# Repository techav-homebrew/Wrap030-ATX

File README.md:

# Wrap030
Homebrew mATX form-factor 68030 computer

# Memory Map

## Normal Operation
This is the space allocated to each device (even if the device will not use the entire address space allocated, such as the PS/2 keyboard controller which uses no address lines). 

| Device            | Start         | End           | Size                      |
| ----------------- | ------------- | ------------- | ------------------------- |
| Main Memory       | `$0000,0000`  | `$7fff,ffff`  | 2048MB (256MB available)  |
| Unused (BERR)     | `$8000,0000`  | `$cfff,ffff`  | 1280MB    |
| Video             | `$d000,0000`  | `$d0ff,ffff`  |   16MB    |
| Unused (BERR)     | `$d100,0000`  | `$d1ff,ffff`  |   16MB    |
| ISA Memory        | `$d200,0000`  | `$d2ff,ffff`  |   16MB    |
| ISA I/O           | `$d300,0000`  | `$d3ff,ffff`  |   16MB    |
| Unused (BERR)     | `$d400,0000`  | `$dbff,ffff`  |  128MB    |
| S/P I/O           | `$dc00,0000`  | `$dcff,ffff`  |   16MB    |
| Reserved (BERR)   | `$dd00,0000`  | `$ddff,ffff`  |   16MB    |
| Keyboard          | `$de00,0000`  | `$deff,ffff`  |   16MB    |
| Reserved (BERR)   | `$df00,0000`  | `$dfff,ffff`  |   16MB    |
| Bus Ctrl Reg      | `$e000,0000`  | `$e0ff,ffff`  |   16MB    |
| DRAM Ctrl Reg     | `$e100,0000`  | `$e1ff,ffff`  |   16MB    |
| IRQ Ctrl Reg      | `$e200,0000`  | `$e2ff,ffff`  |   16MB    |
| Unused (BERR)     | `$e300,0000`  | `$efff,ffff`  |  208MB    |
| ROM               | `$f000,0000`  | `$ffff,ffff`  |  256MB    |

## Reset Overlay
The reset overlay allows ROM to be read from the first 256MB of the CPU address space so the CPU can load the proper startup vectors. While the reset overlay is enabled, DRAM is write-only through the first 256MB (the entire DRAM space available on the Wrap030-ATX board). ROM will continue to be readable in its normal address space. This allows the reset vector to point to ROM at its normal address.

The reset overlay is enabled by default on power on. It is disabled by setting the overlay bit on the bus controller register. 

| Device            | Start         | End           | Notes                       |
| ----------------- | ------------- | ------------- | --------------------------- |
| ROM Overlay       | `$0000,0000`  | `$0fff,ffff`  | Read-only 256MB ROM space   |
| DRAM Overlay      | `$0000,0000`  | `$0fff,ffff`  | Write-Only 256MB DRAM space |
| DRAM              | `$1000,0000`  | `$7fff,ffff`  | Read/Write DRAM space       |
| ROM               | `$f000,0000`  | `$ffff,ffff`  | Read/Write ROM space        |

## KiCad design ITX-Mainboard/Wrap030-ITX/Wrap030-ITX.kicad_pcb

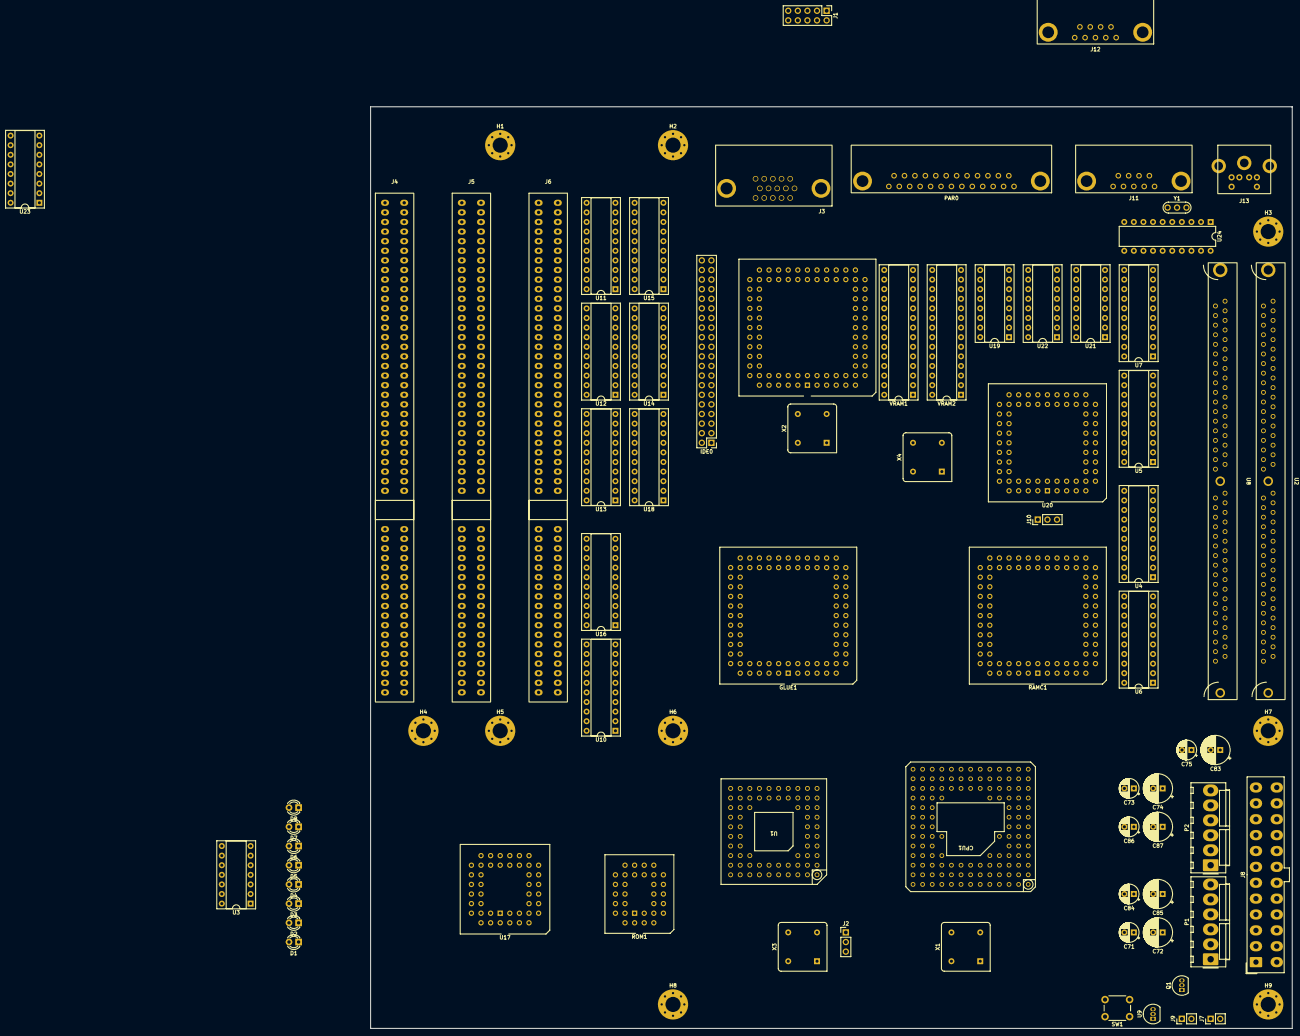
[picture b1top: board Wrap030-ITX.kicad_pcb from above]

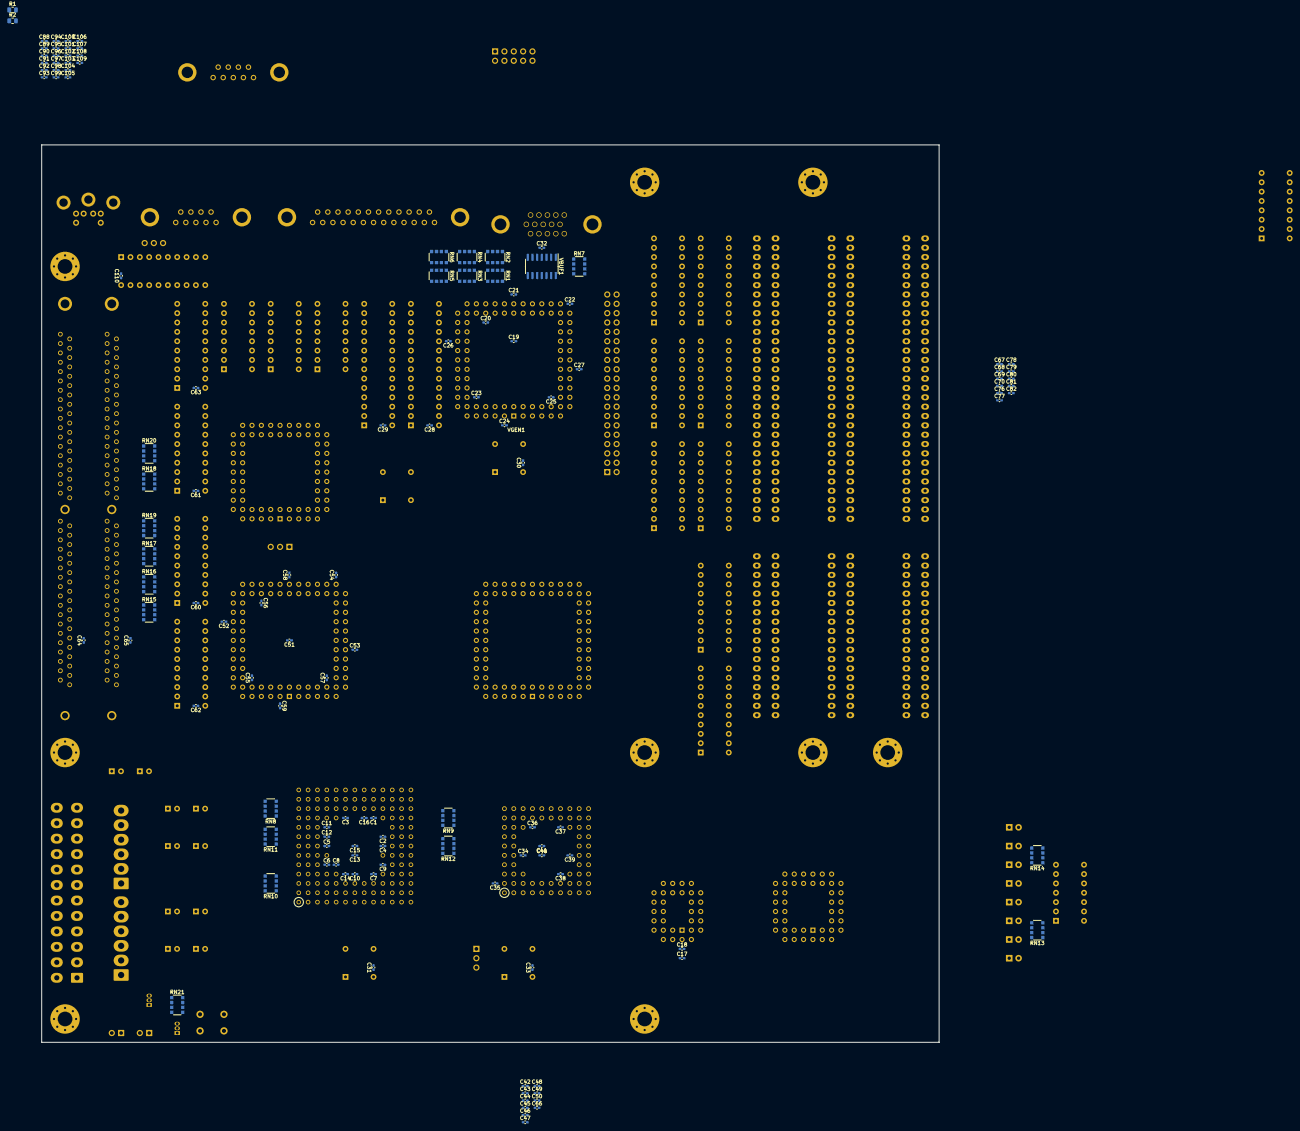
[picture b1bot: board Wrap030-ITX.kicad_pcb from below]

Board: 2 copper layers, 243.8 x 243.8 mm, 206 parts (124 on the bottom side), 386 nets, no tracks yet.

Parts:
C1, C2, C3, C4, C5, C6, C7, C8, C9, C10, C11, C12, C14, C16, C17, C20, C21, C22, C23, C24, C25, C26, C27, C28, C29, C30, C31, C32, C33, C34, C35, C36, C37, C38, C39, C43, C44, C45, C46, C47, C48, C49, C50, C52, C53, C54, C55, C56, C57, C58, C59, C60, C61, C62, C63, C66, C68, C69, C70, C76, C77, C78, C79, C80, C81, C82, C88, C89, C90, C91, C101, C110: 100nF; C_0402_1005Metric_Pad0.74x0.62mm_HandSolder
C13, C15, C18, C19, C40, C41, C42, C51, C64, C65, C67, C92, C102, C103, C104, C105, C106, C107, C108, C109: 1uF; C_0402_1005Metric_Pad0.74x0.62mm_HandSolder
C71, C73, C75, C84, C86: 10uF; CP_Radial_D5.0mm_P2.50mm
C72, C74, C83, C85, C87: 100uF; CP_Radial_D7.5mm_P2.50mm
C93, C94, C95, C96, C97, C98, C99, C100: 2200pF; C_0402_1005Metric_Pad0.74x0.62mm_HandSolder
CPU1: MC68030; PGA128
D1, D2, D3, D4, D5, D6, D7, D8: LED; LED_D3.0mm
GLUE1: ATF1508AS; PLCC-84_THT-Socket
H1, H2, H3, H4, H5, H6, H7, H8, H9: 4mm; MountingHole_4mm_Pad_Via
IDE0: Conn_02x20_Odd_Even; PinHeader_2x20_P2.54mm_Vertical
J1: Conn_02x05_Odd_Even; PinHeader_2x05_P2.54mm_Vertical
J2, J10: Conn_01x03; PinHeader_1x03_P2.54mm_Vertical
J3: DE15_Receptacle_HighDensity_MountingHoles; DE15-HD
J4, J5, J6: Bus_ISA_16bit; ISA16
J7, J9: Conn_01x02; PinHeader_1x02_P2.54mm_Vertical
J8: ATX-24; Molex_Mini-Fit_Jr_5566-24A_2x12_P4.20mm_Vertical
J11, J12: DE9_Plug_MountingHoles; DE9
J13: DIN-6; MiniDIN6
P1, P2: Conn_01x06; Molex_KK-396_A-41791-0006_1x06_P3.96mm_Vertical
PAR0: DB25_Receptacle_MountingHoles; DB25
Q1: PN2222A; TO-92L_Inline
R1, R2: 10k; R_0805_2012Metric
RAMC1: ATF1508AS; PLCC-84_THT-Socket
RN1, RN2, RN3, RN4, RN5, RN6, RN8, RN9, RN10, RN11, RN12: YC164-FR-071KL; R_Array_Convex_4x1206
RN7: YC164-FR-0775RL; R_Array_Convex_4x1206
RN13, RN14, RN21: YC124-JR-07220RL; R_Array_Convex_4x1206
RN15, RN16, RN17, RN18, RN19, RN20: YC124-JR-1033RL; R_Array_Convex_4x1206
ROM1: SST39SF040; PLCC-32_THT-Socket
SW1: SW_Push; SW_PUSH_6mm
U1: MC68882; PGA68
U2, U8: TE-822021-4; SIMM72
U3: 74HCT04; DIP-14_W7.62mm_Socket
U4, U5, U6, U7, U10, U11, U12: 74HC245; DIP-20_W7.62mm_Socket
U9: DS1813-5+T&R; TO-92_Inline
U13, U14, U15: 74LS573; DIP-20_W7.62mm_Socket
U16: 74AHCT244; DIP-20_W7.62mm_Socket
U17: ATF1504; PLCC-44_THT-Socket
U18: 74HCT688; DIP-20_W7.62mm_Socket
U19: 74LS139; DIP-16_W7.62mm_Socket
U20: WD16C552; PLCC-68_THT-Socket
U21, U22: MAX232; DIP-16_W7.62mm_Socket
U23: 74LS148; DIP-16_W7.62mm_Socket
U24: ATtiny2313A-PU; DIP-20_W7.62mm
VBUF1: ADA4891-4; SOIC-14_3.9x8.7mm_P1.27mm
VGEN1: ATF1508AS; PLCC-84_THT-Socket
VRAM1, VRAM2: CY62256-70PC; DIP-28_W7.62mm_Socket
X1: 50M; Oscillator_DIP-8
X2: 25.175M; Oscillator_DIP-8
X3: 16M; Oscillator_DIP-8
X4: 1.6862M; Oscillator_DIP-8
Y1: 16M; Resonator-3Pin_W7.0mm_H2.5mm

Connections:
+5VP: C75.1, C83.1, J8.9 (+5VSB), RN14.4 (R4.1)
+12V: C71.1, C72.1, J4.9 (+12V), J5.9 (+12V), J6.9 (+12V), J8.10 (+12V), J8.11 (+12V), P1.3
-5V: C86.2, C87.2, J4.5 (-5V), J5.5 (-5V), J6.5 (-5V), P2.3
-12V: C84.2, C85.2, J4.7 (-12V), J5.7 (-12V), J6.7 (-12V), J8.14 (-12V), P1.4
/CPU-FPU/FPU-CLK: J2.3, X3.5 (OUT)
/ISA-IDE/ISA-A0: IDE0.35, J4.62 (BA00), J5.62 (BA00), J6.62 (BA00), U13.19 (Q0)
/ISA-IDE/ISA-A1: IDE0.33, J4.61 (BA01), J5.61 (BA01), J6.61 (BA01), U13.18 (Q1)
/ISA-IDE/ISA-A2: IDE0.36, J4.60 (BA02), J5.60 (BA02), J6.60 (BA02), U13.17 (Q2)
/ISA-IDE/ISA-A3: J4.59 (BA03), J5.59 (BA03), J6.59 (BA03), U13.16 (Q3), U18.2 (P0)
/ISA-IDE/ISA-A4: J4.58 (BA04), J5.58 (BA04), J6.58 (BA04), U13.15 (Q4), U18.4 (P1)
/ISA-IDE/ISA-A5: J4.57 (BA05), J5.57 (BA05), J6.57 (BA05), U13.14 (Q5), U18.6 (P2)
/ISA-IDE/ISA-A6: J4.56 (BA06), J5.56 (BA06), J6.56 (BA06), U13.13 (Q6), U18.8 (P3)
/ISA-IDE/ISA-A7: J4.55 (BA07), J5.55 (BA07), J6.55 (BA07), U13.12 (Q7), U18.11 (P4)
/ISA-IDE/ISA-A8: J4.54 (BA08), J5.54 (BA08), J6.54 (BA08), U14.19 (Q0), U18.13 (P5)
/ISA-IDE/ISA-A9: J4.53 (BA09), J5.53 (BA09), J6.53 (BA09), U14.18 (Q1), U19.2 (A0)
/ISA-IDE/ISA-A10: J4.52 (BA10), J5.52 (BA10), J6.52 (BA10), U14.17 (Q2)
/ISA-IDE/ISA-A11: J4.51 (BA11), J5.51 (BA11), J6.51 (BA11), U14.16 (Q3)
/ISA-IDE/ISA-A12: J4.50 (BA12), J5.50 (BA12), J6.50 (BA12), U14.15 (Q4)
/ISA-IDE/ISA-A13: J4.49 (BA13), J5.49 (BA13), J6.49 (BA13), U14.14 (Q5)
/ISA-IDE/ISA-A14: J4.48 (BA14), J5.48 (BA14), J6.48 (BA14), U14.13 (Q6)
/ISA-IDE/ISA-A15: J4.47 (BA15), J5.47 (BA15), J6.47 (BA15), U14.12 (Q7)
/ISA-IDE/ISA-A16: J4.46 (BA16), J5.46 (BA16), J6.46 (BA16), U15.19 (Q0)
/ISA-IDE/ISA-A17: J4.45 (BA17), J5.45 (BA17), J6.45 (BA17), U15.18 (Q1)
/ISA-IDE/ISA-A18: J4.44 (BA18), J5.44 (BA18), J6.44 (BA18), U15.17 (Q2)
/ISA-IDE/ISA-A19: J4.43 (BA19), J5.43 (BA19), J6.43 (BA19), U15.16 (Q3)
/ISA-IDE/ISA-AEN: J4.28 (ALE), J5.28 (ALE), J6.28 (ALE), U13.1 (OE), U14.1 (OE), U15.1 (OE), U16.1 (1OE), U16.19 (2OE), U17.20 (IO19)
/ISA-IDE/ISA-ALE: J4.42 (AEN), J5.42 (AEN), J6.42 (AEN), U13.11 (Load), U14.11 (Load), U15.11 (Load), U17.21 (IO17)
/ISA-IDE/ISA-CLK: J4.20 (CLK), J5.20 (CLK), J6.20 (CLK), U17.25 (IO35)
/ISA-IDE/ISA-D0: IDE0.3, J4.40 (DB0), J5.40 (DB0), J6.40 (DB0), U11.2 (A0), U12.2 (A0)
/ISA-IDE/ISA-D1: IDE0.5, J4.39 (DB1), J5.39 (DB1), J6.39 (DB1), U11.3 (A1), U12.3 (A1)
/ISA-IDE/ISA-D2: IDE0.7, J4.38 (DB2), J5.38 (DB2), J6.38 (DB2), U11.4 (A2), U12.4 (A2)
/ISA-IDE/ISA-D3: IDE0.9, J4.37 (DB3), J5.37 (DB3), J6.37 (DB3), U11.5 (A3), U12.5 (A3)
/ISA-IDE/ISA-D4: IDE0.11, J4.36 (DB4), J5.36 (DB4), J6.36 (DB4), U11.6 (A4), U12.6 (A4)
/ISA-IDE/ISA-D5: IDE0.13, J4.35 (DB5), J5.35 (DB5), J6.35 (DB5), U11.7 (A5), U12.7 (A5)
/ISA-IDE/ISA-D6: IDE0.15, J4.34 (DB6), J5.34 (DB6), J6.34 (DB6), U11.8 (A6), U12.8 (A6)
/ISA-IDE/ISA-D7: IDE0.17, J4.33 (DB7), J5.33 (DB7), J6.33 (DB7), U11.9 (A7), U12.9 (A7)
/ISA-IDE/ISA-D8: IDE0.4, J4.91 (D8), J5.91 (D8), J6.91 (D8), U10.2 (A0)
/ISA-IDE/ISA-D9: IDE0.6, J4.92 (D9), J5.92 (D9), J6.92 (D9), U10.3 (A1)
/ISA-IDE/ISA-D10: IDE0.8, J4.93 (D10), J5.93 (D10), J6.93 (D10), U10.4 (A2)
/ISA-IDE/ISA-D11: IDE0.10, J4.94 (D11), J5.94 (D11), J6.94 (D11), U10.5 (A3)
/ISA-IDE/ISA-D12: IDE0.12, J4.95 (D12), J5.95 (D12), J6.95 (D12), U10.6 (A4)
/ISA-IDE/ISA-D13: IDE0.14, J4.96 (D13), J5.96 (D13), J6.96 (D13), U10.7 (A5)
/ISA-IDE/ISA-D14: IDE0.16, J4.97 (D14), J5.97 (D14), J6.97 (D14), U10.8 (A6)
/ISA-IDE/ISA-D15: IDE0.18, J4.98 (D15), J5.98 (D15), J6.98 (D15), U10.9 (A7)
/ISA-IDE/ISA-IDE-Connectors/ISA-OSC: J4.30 (OSC), J5.30 (OSC), J6.30 (OSC)
/ISA-IDE/ISA-IDE-Connectors/~IDE-DMACK: IDE0.29, R2.2
/ISA-IDE/ISA-IORDY: IDE0.27, J4.41 (IO_READY), J5.41 (IO_READY), J6.41 (IO_READY), R1.2, U17.29 (IO41)
/ISA-IDE/ISA-LA17: J4.88 (LA17), J5.88 (LA17), J6.88 (LA17), U16.18 (1Y0)
/ISA-IDE/ISA-LA18: J4.87 (LA18), J5.87 (LA18), J6.87 (LA18), U16.16 (1Y1)
/ISA-IDE/ISA-LA19: J4.86 (LA19), J5.86 (LA19), J6.86 (LA19), U16.14 (1Y2)
/ISA-IDE/ISA-LA20: J4.85 (LA20), J5.85 (LA20), J6.85 (LA20), U16.12 (1Y3)
/ISA-IDE/ISA-LA21: J4.84 (LA21), J5.84 (LA21), J6.84 (LA21), U16.3 (2Y0)
/ISA-IDE/ISA-LA22: J4.83 (LA22), J5.83 (LA22), J6.83 (LA22), U16.5 (2Y1)
/ISA-IDE/ISA-LA23: J4.82 (LA23), J5.82 (LA23), J6.82 (LA23), U16.7 (2Y2)
/ISA-IDE/ISA-MASTER: J4.79 (MASTER), J5.79 (MASTER), J6.79 (MASTER), U17.28 (IO40)
/ISA-IDE/ISA-RESET: IDE0.1, J4.2 (RESET), J5.2 (RESET), J6.2 (RESET), U17.19 (IO20)
/ISA-IDE/ISA-SBHE: J4.81 (SBHE), J5.81 (SBHE), J6.81 (SBHE), U17.18 (IO21)
/ISA-IDE/~IDE-CS1: IDE0.37, U19.4 (O0)
/ISA-IDE/~IDE-CS3: IDE0.38, U19.5 (O1)
/ISA-IDE/~ISA-IOCS16: IDE0.32, J4.64 (~IOCS16), J5.64 (~IOCS16), J6.64 (~IOCS16), U17.27 (IO37)
/ISA-IDE/~ISA-IOR: IDE0.25, J4.14 (~IOR), J5.14 (~IOR), J6.14 (~IOR), U17.24 (IO33)
/ISA-IDE/~ISA-IOW: IDE0.23, J4.13 (~IOW), J5.13 (~IOW), J6.13 (~IOW), U17.14 (IO30)
/ISA-IDE/~ISA-MEMCS16: J4.63 (~MEMCS16), J5.63 (~MEMCS16), J6.63 (~MEMCS16), U17.26 (IO36)
/ISA-IDE/~ISA-MEMR: J4.12 (~SMEMR), J4.89 (~MEMR), J5.12 (~SMEMR), J5.89 (~MEMR), J6.12 (~SMEMR), J6.89 (~MEMR), U17.17 (IO24)
/ISA-IDE/~ISA-MEMW: J4.11 (~SMEMW), J4.90 (~MEMW), J5.11 (~SMEMW), J5.90 (~MEMW), J6.11 (~SMEMW), J6.90 (~MEMW), U17.16 (IO25)
/ISA-IDE/~ISA-XFER8: U10.19 (CE), U17.5 (IO14)
/ISA-IDE/~ISA-XFER16: U11.19 (CE), U12.19 (CE), U17.4 (IO16)
/Keyboard/PS2-CLK: J13.5, U24.7 (PD3)
/Keyboard/PS2-DAT: J13.1, U24.8 (PD4)
/Main-Memory/MEM-A0: RAMC1.4 (IO16), RN15.1 (R1.1)
/Main-Memory/MEM-A0R: RN15.8 (R1.2), U2.12 (A0), U8.12 (A0)
/Main-Memory/MEM-A1: RAMC1.22 (IO17), RN15.2 (R2.1)
/Main-Memory/MEM-A1R: RN15.7 (R2.2), U2.13 (A1), U8.13 (A1)
/Main-Memory/MEM-A2: RAMC1.21 (IO19), RN15.3 (R3.1)
/Main-Memory/MEM-A2R: RN15.6 (R3.2), U2.14 (A2), U8.14 (A2)
/Main-Memory/MEM-A3: RAMC1.20 (IO21), RN15.4 (R4.1)
/Main-Memory/MEM-A3R: RN15.5 (R4.2), U2.15 (A3), U8.15 (A3)
/Main-Memory/MEM-A4: RAMC1.18 (IO24), RN16.1 (R1.1)
/Main-Memory/MEM-A4R: RN16.8 (R1.2), U2.16 (A4), U8.16 (A4)
/Main-Memory/MEM-A5: RAMC1.17 (IO25), RN16.2 (R2.1)
/Main-Memory/MEM-A5R: RN16.7 (R2.2), U2.17 (A5), U8.17 (A5)
/Main-Memory/MEM-A6: RAMC1.16 (IO27), RN16.3 (R3.1)
/Main-Memory/MEM-A6R: RN16.6 (R3.2), U2.18 (A6), U8.18 (A6)
/Main-Memory/MEM-A7: RAMC1.15 (IO29), RN16.4 (R4.1)
/Main-Memory/MEM-A7R: RN16.5 (R4.2), U2.28 (A7), U8.28 (A7)
/Main-Memory/MEM-A8: RAMC1.31 (IO35), RN17.1 (R1.1)
/Main-Memory/MEM-A8R: RN17.8 (R1.2), U2.31 (A8), U8.31 (A8)
/Main-Memory/MEM-A9: RAMC1.30 (IO37), RN17.2 (R2.1)
/Main-Memory/MEM-A9R: RN17.7 (R2.2), U2.32 (A9), U8.32 (A9)
/Main-Memory/MEM-A10: RAMC1.29 (IO38), RN17.3 (R3.1)
/Main-Memory/MEM-A10R: RN17.6 (R3.2), U2.19 (A10), U8.19 (A10)
/Main-Memory/MEM-A11: RAMC1.28 (IO40), RN17.4 (R4.1)
/Main-Memory/MEM-A11R: RN17.5 (R4.2), U2.29 (A11), U8.29 (A11)
/Main-Memory/MEM-D0: U2.2 (D0), U4.2 (A0), U8.2 (D0)
/Main-Memory/MEM-D1: U2.4 (D1), U4.3 (A1), U8.4 (D1)
/Main-Memory/MEM-D2: U2.6 (D2), U4.4 (A2), U8.6 (D2)
/Main-Memory/MEM-D3: U2.8 (D3), U4.5 (A3), U8.8 (D3)
/Main-Memory/MEM-D4: U2.20 (D4), U4.6 (A4), U8.20 (D4)
/Main-Memory/MEM-D5: U2.22 (D5), U4.7 (A5), U8.22 (D5)
/Main-Memory/MEM-D6: U2.24 (D6), U4.8 (A6), U8.24 (D6)
/Main-Memory/MEM-D7: U2.26 (D7), U4.9 (A7), U8.26 (D7)
/Main-Memory/MEM-D8: U2.49 (D8), U5.2 (A0), U8.49 (D8)
/Main-Memory/MEM-D9: U2.51 (D9), U5.3 (A1), U8.51 (D9)
/Main-Memory/MEM-D10: U2.53 (D10), U5.4 (A2), U8.53 (D10)
/Main-Memory/MEM-D11: U2.55 (D11), U5.5 (A3), U8.55 (D11)
/Main-Memory/MEM-D12: U2.57 (D12), U5.6 (A4), U8.57 (D12)
/Main-Memory/MEM-D13: U2.61 (D13), U5.7 (A5), U8.61 (D13)
/Main-Memory/MEM-D14: U2.63 (D14), U5.8 (A6), U8.63 (D14)
/Main-Memory/MEM-D15: U2.65 (D15), U5.9 (A7), U8.65 (D15)
/Main-Memory/MEM-D16: U2.3 (D16), U6.2 (A0), U8.3 (D16)
/Main-Memory/MEM-D17: U2.5 (D17), U6.3 (A1), U8.5 (D17)
/Main-Memory/MEM-D18: U2.7 (D18), U6.4 (A2), U8.7 (D18)
/Main-Memory/MEM-D19: U2.9 (D19), U6.5 (A3), U8.9 (D19)
/Main-Memory/MEM-D20: U2.21 (D20), U6.6 (A4), U8.21 (D20)
/Main-Memory/MEM-D21: U2.23 (D21), U6.7 (A5), U8.23 (D21)
/Main-Memory/MEM-D22: U2.25 (D22), U6.8 (A6), U8.25 (D22)
/Main-Memory/MEM-D23: U2.27 (D23), U6.9 (A7), U8.27 (D23)
/Main-Memory/MEM-D24: U2.50 (D24), U7.2 (A0), U8.50 (D24)
/Main-Memory/MEM-D25: U2.52 (D25), U7.3 (A1), U8.52 (D25)
/Main-Memory/MEM-D26: U2.54 (D26), U7.4 (A2), U8.54 (D26)
/Main-Memory/MEM-D27: U2.56 (D27), U7.5 (A3), U8.56 (D27)
/Main-Memory/MEM-D28: U2.58 (D28), U7.6 (A4), U8.58 (D28)
/Main-Memory/MEM-D29: U2.60 (D29), U7.7 (A5), U8.60 (D29)
/Main-Memory/MEM-D30: U2.62 (D30), U7.8 (A6), U8.62 (D30)
/Main-Memory/MEM-D31: U2.64 (D31), U7.9 (A7), U8.64 (D31)
/Main-Memory/~MEM-CAS0R: RN18.8 (R1.2), U2.40 (~CAS0), U8.40 (~CAS0)
/Main-Memory/~MEM-CAS0: RAMC1.40 (IO51), RN18.1 (R1.1)
/Main-Memory/~MEM-CAS1R: RN18.7 (R2.2), U2.43 (~CAS1), U8.43 (~CAS1)
/Main-Memory/~MEM-CAS1: RAMC1.39 (IO53), RN18.2 (R2.1)
/Main-Memory/~MEM-CAS2R: RN18.6 (R3.2), U2.41 (~CAS2), U8.41 (~CAS2)
/Main-Memory/~MEM-CAS2: RAMC1.37 (IO56), RN18.3 (R3.1)
/Main-Memory/~MEM-CAS3R: RN18.5 (R4.2), U2.42 (~CAS3), U8.42 (~CAS3)
/Main-Memory/~MEM-CAS3: RAMC1.36 (IO57), RN18.4 (R4.1)
/Main-Memory/~MEM-RAS0R: RN19.8 (R1.2), U2.34 (~RAS2), U2.44 (~RAS0)
/Main-Memory/~MEM-RAS0: RAMC1.27 (IO43), RN19.1 (R1.1)
/Main-Memory/~MEM-RAS1R: RN19.7 (R2.2), U2.33 (~RAS3), U2.45 (~RAS1)
/Main-Memory/~MEM-RAS1: RAMC1.25 (IO45), RN19.2 (R2.1)
/Main-Memory/~MEM-RAS2R: RN19.6 (R3.2), U8.34 (~RAS2), U8.44 (~RAS0)
/Main-Memory/~MEM-RAS2: RAMC1.24 (IO46), RN19.3 (R3.1)
/Main-Memory/~MEM-RAS3R: RN19.5 (R4.2), U8.33 (~RAS3), U8.45 (~RAS1)
/Main-Memory/~MEM-RAS3: RAMC1.41 (IO49), RN19.4 (R4.1)
/Main-Memory/~MEM-WER: RN20.8 (R1.2), U2.47 (~WE), U8.47 (~WE)
/Main-Memory/~MEM-WE: RAMC1.35 (IO59), RN20.1 (R1.1), U4.1 (A->B), U5.1 (A->B), U6.1 (A->B), U7.1 (A->B)
/Power-Supply/PWR_ON_R: Q1.2 (B), RN21.8 (R1.2)
/Power-Supply/~PWR_ON: J7.2, J8.16 (PS_ON#), Q1.3 (C)
/Serial-Parallel-IO/COM0-C1M: C102.2, U21.3 (C1-)
/Serial-Parallel-IO/COM0-C1P: C102.1, U21.1 (C1+)
/Serial-Parallel-IO/COM0-C2M: C103.1, U21.5 (C2-)
/Serial-Parallel-IO/COM0-C2P: C103.2, U21.4 (C2+)
/Serial-Parallel-IO/COM0-CTS232: J11.8, U21.8 (R2IN)
/Serial-Parallel-IO/COM0-RTS232: J11.7, U21.7 (T2OUT)
/Serial-Parallel-IO/COM0-RX232: J11.2, U21.13 (R1IN)
/Serial-Parallel-IO/COM0-SIN: U20.41 (SIN0), U21.12 (R1OUT)
/Serial-Parallel-IO/COM0-SOUT: U20.26 (SOUT0), U21.11 (T1IN)
/Serial-Parallel-IO/COM0-TX232: J11.3, U21.14 (T1OUT)
/Serial-Parallel-IO/COM0-VM: C105.1, U21.6 (VS-)
/Serial-Parallel-IO/COM0-VP: C104.1, U21.2 (VS+)
/Serial-Parallel-IO/COM1-C1M: C106.2, U22.3 (C1-)
/Serial-Parallel-IO/COM1-C1P: C106.1, U22.1 (C1+)
/Serial-Parallel-IO/COM1-C2M: C109.1, U22.5 (C2-)
/Serial-Parallel-IO/COM1-C2P: C109.2, U22.4 (C2+)
/Serial-Parallel-IO/COM1-CTS232: J12.8, U22.8 (R2IN)
/Serial-Parallel-IO/COM1-RTS232: J12.7, U22.7 (T2OUT)
/Serial-Parallel-IO/COM1-RX232: J12.2, U22.13 (R1IN)
/Serial-Parallel-IO/COM1-SIN: U20.62 (SIN1), U22.12 (R1OUT)
/Serial-Parallel-IO/COM1-SOUT: U20.10 (SOUT1), U22.11 (T1IN)
/Serial-Parallel-IO/COM1-TX232: J12.3, U22.14 (T1OUT)
/Serial-Parallel-IO/COM1-VM: C108.1, U22.6 (VS-)
/Serial-Parallel-IO/COM1-VP: C107.1, U22.2 (VS+)
/Serial-Parallel-IO/PAR-BIDEN: J10.2, U20.1 (BIDEN)
/Serial-Parallel-IO/PAR-BUSY: PAR0.11, U20.66 (BUSY)
/Serial-Parallel-IO/PAR-D0: C93.1, U20.53 (PD0)
/Serial-Parallel-IO/PAR-D0-C: C93.2, PAR0.2
/Serial-Parallel-IO/PAR-D1: C94.1, U20.52 (PD1)
/Serial-Parallel-IO/PAR-D1-C: C94.2, PAR0.3
/Serial-Parallel-IO/PAR-D2: C95.1, U20.51 (PD2)
/Serial-Parallel-IO/PAR-D2-C: C95.2, PAR0.4
/Serial-Parallel-IO/PAR-D3: C96.1, U20.50 (PD3)
/Serial-Parallel-IO/PAR-D3-C: C96.2, PAR0.5
/Serial-Parallel-IO/PAR-D4: C97.1, U20.49 (PD4)
/Serial-Parallel-IO/PAR-D4-C: C97.2, PAR0.6
/Serial-Parallel-IO/PAR-D5: C98.1, U20.48 (PD5)
/Serial-Parallel-IO/PAR-D5-C: C98.2, PAR0.7
/Serial-Parallel-IO/PAR-D6: C99.1, U20.47 (PD6)
/Serial-Parallel-IO/PAR-D6-C: C99.2, PAR0.8
/Serial-Parallel-IO/PAR-D7: C100.1, U20.46 (PD7)
/Serial-Parallel-IO/PAR-D7-C: C100.2, PAR0.9
/Serial-Parallel-IO/PAR-PE: PAR0.12, U20.67 (PE)
/Serial-Parallel-IO/PAR-SLCT: PAR0.13, U20.65 (SLCT)
/Serial-Parallel-IO/SPIO-CLK: U20.4 (COM-CLK), X4.5 (OUT)
/Serial-Parallel-IO/~COM0-CTS: U20.28 (~CTS0), U21.9 (R2OUT)
/Serial-Parallel-IO/~COM0-RTS: U20.24 (~RTS0), U21.10 (T2IN)
/Serial-Parallel-IO/~COM1-CTS: U20.13 (~CTS1), U22.9 (R2OUT)
/Serial-Parallel-IO/~COM1-RTS: U20.12 (~RTS1), U22.10 (T2IN)
/Serial-Parallel-IO/~PAR-ACK: PAR0.10, U20.68 (~ACK)
/Serial-Parallel-IO/~PAR-AFD: PAR0.14, U20.56 (~AFD)
/Serial-Parallel-IO/~PAR-ERR: PAR0.15, U20.63 (~ERR)
/Serial-Parallel-IO/~PAR-INIT: PAR0.16, U20.57 (~INIT)
/Serial-Parallel-IO/~PAR-SLIN: PAR0.17, U20.58 (~SLIN)
/Serial-Parallel-IO/~PAR-STB: PAR0.1, U20.55 (~STB)
/Serial-Parallel-IO/~SPIO-CS0: U19.12 (O0), U20.32 (~CS0)
/Serial-Parallel-IO/~SPIO-CS1: U19.11 (O1), U20.3 (~CS1)
/Serial-Parallel-IO/~SPIO-CS2: U19.10 (O2), U20.38 (~CS2)
/VidGen/VID-B-A: RN5.2 (R2.1), RN5.3 (R3.1), RN5.4 (R4.1), VBUF1.12 (IN4_P)
/VidGen/VID-B-D: RN5.1 (R1.1), VGEN1.51 (IO77)
/VidGen/VID-B-D1: RN5.7 (R2.2), RN5.8 (R1.2)
/VidGen/VID-B-OUT: J1.6, J3.3, RN7.6 (R3.2)
/VidGen/VID-G-A: RN3.2 (R2.1), RN3.3 (R3.1), RN3.4 (R4.1), VBUF1.10 (IN3_P)
/VidGen/VID-G-D: RN3.1 (R1.1), VGEN1.49 (IO73)
/VidGen/VID-G-D1: RN3.7 (R2.2), RN3.8 (R1.2)
/VidGen/VID-G-OUT: J1.8, J3.2, RN7.7 (R2.2)
/VidGen/VID-H: J1.4, J3.13, VGEN1.50 (IO75)
/VidGen/VID-I-D: RN2.7 (R2.2), RN4.7 (R2.2), RN6.7 (R2.2), VGEN1.46 (IO69)
/VidGen/VID-I-D1B: RN6.1 (R1.1), RN6.2 (R2.1)
/VidGen/VID-I-D1G: RN4.1 (R1.1), RN4.2 (R2.1)
/VidGen/VID-I-D1R: RN2.1 (R1.1), RN2.2 (R2.1)
/VidGen/VID-I-D2B: RN5.6 (R3.2), RN6.6 (R3.2), RN6.8 (R1.2)
/VidGen/VID-I-D2G: RN3.6 (R3.2), RN4.6 (R3.2), RN4.8 (R1.2)
/VidGen/VID-I-D2R: RN1.6 (R3.2), RN2.6 (R3.2), RN2.8 (R1.2)
/VidGen/VID-I-D3B: RN6.3 (R3.1), RN6.4 (R4.1)
/VidGen/VID-I-D3G: RN4.3 (R3.1), RN4.4 (R4.1)
/VidGen/VID-I-D3R: RN2.3 (R3.1), RN2.4 (R4.1)
/VidGen/VID-R-A: RN1.2 (R2.1), RN1.3 (R3.1), RN1.4 (R4.1), VBUF1.5 (IN2_P)
/VidGen/VID-R-D: RN1.1 (R1.1), VGEN1.45 (IO67)
/VidGen/VID-R-D1: RN1.7 (R2.2), RN1.8 (R1.2)
/VidGen/VID-R-OUT: J1.10, J3.1, RN7.8 (R1.2)
/VidGen/VID-V: J1.2, J3.14, VGEN1.48 (IO72)
/VidGen/VID_A0: VGEN1.30 (IO37), VRAM1.10 (A0), VRAM2.10 (A0)
/VidGen/VID_A1: VGEN1.28 (IO40), VRAM1.9 (A1), VRAM2.9 (A1)
/VidGen/VID_A2: VGEN1.27 (IO43), VRAM1.8 (A2), VRAM2.8 (A2)
/VidGen/VID_A3: VGEN1.25 (IO45), VRAM1.7 (A3), VRAM2.7 (A3)
/VidGen/VID_A4: VGEN1.21 (IO19), VRAM1.6 (A4), VRAM2.6 (A4)
/VidGen/VID_A5: VGEN1.8 (IO11), VRAM1.5 (A5), VRAM2.5 (A5)
/VidGen/VID_A6: VGEN1.17 (IO25), VRAM1.4 (A6), VRAM2.4 (A6)
/VidGen/VID_A7: VGEN1.10 (IO6), VRAM1.3 (A7), VRAM2.3 (A7)
/VidGen/VID_A8: VGEN1.16 (IO27), VRAM1.25 (A8), VRAM2.25 (A8)
/VidGen/VID_A9: VGEN1.18 (IO24), VRAM1.24 (A9), VRAM2.24 (A9)
/VidGen/VID_A10: VGEN1.24 (IO46), VRAM1.21 (A10), VRAM2.21 (A10)
/VidGen/VID_A11: VGEN1.20 (IO21), VRAM1.23 (A11), VRAM2.23 (A11)
/VidGen/VID_A12: VGEN1.11 (IO5), VRAM1.2 (A12), VRAM2.2 (A12)
/VidGen/VID_A13: VGEN1.15 (IO29), VRAM1.26 (A13), VRAM2.26 (A13)
/VidGen/VID_A14: VGEN1.9 (IO8), VRAM1.1 (A14), VRAM2.1 (A14)
/VidGen/VID_CLK: VGEN1.83 (GCLK1), X2.5 (OUT)
/VidGen/VID_D0: VGEN1.34 (IO61), VRAM1.11 (Q0), VRAM2.11 (Q0)
/VidGen/VID_D1: VGEN1.35 (IO59), VRAM1.12 (Q1), VRAM2.12 (Q1)
/VidGen/VID_D2: VGEN1.40 (IO51), VRAM1.13 (Q2), VRAM2.13 (Q2)
/VidGen/VID_D3: VGEN1.39 (IO53), VRAM1.15 (Q3), VRAM2.15 (Q3)
/VidGen/VID_D4: VGEN1.37 (IO56), VRAM1.16 (Q4), VRAM2.16 (Q4)
/VidGen/VID_D5: VGEN1.33 (IO64), VRAM1.17 (Q5), VRAM2.17 (Q5)
/VidGen/VID_D6: VGEN1.36 (IO57), VRAM1.18 (Q6), VRAM2.18 (Q6)
/VidGen/VID_D7: VGEN1.31 (IO35), VRAM1.19 (Q7), VRAM2.19 (Q7)
/VidGen/~VID_CS0: VGEN1.29 (IO38), VRAM1.20 (~CS)
/VidGen/~VID_CS1: VGEN1.44 (IO65), VRAM2.20 (~CS)
/VidGen/~VID_RD: VGEN1.22 (IO17), VRAM1.22 (~OE), VRAM2.22 (~OE)
/VidGen/~VID_WR: VGEN1.12 (IO3), VRAM1.27 (~WE), VRAM2.27 (~WE)
CPU-A0: CPU1.A2 (A0), GLUE1.65 (IO101), RAMC1.44 (IO65), ROM1.12 (A0), U13.2 (D0), VGEN1.4 (IO16)
CPU-A1: CPU1.C4 (A1), GLUE1.67 (IO104), RAMC1.45 (IO67), ROM1.11 (A1), U1.K1 (A1), U13.3 (D1), VGEN1.55 (IO85)
CPU-A2: CPU1.D13 (A2), RAMC1.46 (IO69), ROM1.10 (A2), U1.H2 (A2), U13.4 (D2), VGEN1.54 (IO83)
CPU-A3: CPU1.D12 (A3), RAMC1.48 (IO72), ROM1.9 (A3), U1.J1 (A3), U13.5 (D3), U20.35 (A0), VGEN1.57 (IO88)
CPU-A4: CPU1.C13 (A4), RAMC1.49 (IO73), ROM1.8 (A4), U1.G2 (A4), U13.6 (D4), U20.34 (A1), VGEN1.56 (IO86)
CPU-A5: CPU1.C12 (A5), RAMC1.50 (IO75), ROM1.7 (A5), U13.7 (D5), U20.33 (A2), VGEN1.58 (IO91)
CPU-A6: CPU1.D11 (A6), RAMC1.51 (IO77), ROM1.6 (A6), U13.8 (D6), U19.13 (A1), VGEN1.61 (IO94)
CPU-A7: CPU1.B13 (A7), RAMC1.52 (IO80), ROM1.5 (A7), U13.9 (D7), U19.14 (A0), VGEN1.60 (IO93)
CPU-A8: CPU1.B12 (A8), RAMC1.54 (IO83), ROM1.27 (A8), U14.2 (D0), VGEN1.63 (IO97)
CPU-A9: CPU1.C11 (A9), RAMC1.55 (IO85), ROM1.26 (A9), U14.3 (D1), VGEN1.65 (IO101)
CPU-A10: CPU1.A13 (A10), RAMC1.56 (IO86), ROM1.23 (A10), U14.4 (D2), VGEN1.64 (IO99)
CPU-A11: CPU1.C10 (A11), RAMC1.57 (IO88), ROM1.25 (A11), U14.5 (D3), VGEN1.67 (IO104)
CPU-A12: CPU1.B11 (A12), RAMC1.58 (IO91), ROM1.4 (A12), U14.6 (D4), VGEN1.68 (IO105)
CPU-A13: CPU1.A12 (A13), RAMC1.60 (IO93), ROM1.28 (A13), U14.7 (D5), VGEN1.69 (IO107)
CPU-A14: CPU1.B10 (A14), RAMC1.61 (IO94), ROM1.29 (A14), U14.8 (D6), VGEN1.70 (IO109)
CPU-A15: CPU1.A11 (A15), RAMC1.63 (IO97), ROM1.3 (A15), U14.9 (D7), VGEN1.52 (IO80)
CPU-A16: CPU1.B9 (A16), RAMC1.64 (IO99), ROM1.2 (A16), U15.2 (D0)
CPU-A17: CPU1.A10 (A17), RAMC1.65 (IO101), ROM1.30 (A17), U15.3 (D1), U16.2 (1A0)
CPU-A18: CPU1.C8 (A18), RAMC1.67 (IO104), ROM1.1 (A18), U15.4 (D2), U16.4 (1A1)
CPU-A19: CPU1.A9 (A19), RAMC1.68 (IO105), U15.5 (D3), U16.6 (1A2)
CPU-A20: CPU1.B8 (A20), RAMC1.69 (IO107), U16.8 (1A3)
CPU-A21: CPU1.A8 (A21), GLUE1.68 (IO105), RAMC1.70 (IO109), U16.17 (2A0)
CPU-A22: CPU1.B7 (A22), GLUE1.69 (IO107), RAMC1.73 (IO115), U16.15 (2A1)
CPU-A23: CPU1.A7 (A23), GLUE1.70 (IO109), RAMC1.74 (IO117), U16.13 (2A2)
CPU-A24: CPU1.A6 (A24), GLUE1.73 (IO115), RAMC1.75 (IO118)
CPU-A25: CPU1.B6 (A25), GLUE1.74 (IO117), RAMC1.76 (IO120)
CPU-A26: CPU1.A5 (A26), GLUE1.75 (IO118), RAMC1.77 (IO123)
CPU-A27: CPU1.B5 (A27), GLUE1.76 (IO120), RAMC1.79 (IO125)
CPU-A28: CPU1.A4 (A28), GLUE1.77 (IO123), RAMC1.80 (IO126)
CPU-A29: CPU1.B4 (A29), GLUE1.79 (IO125), RAMC1.81 (IO128)
CPU-A30: CPU1.A3 (A30), GLUE1.80 (IO126)
CPU-A31: CPU1.B3 (A31), GLUE1.81 (IO128)
CPU-CLK: CPU1.E1 (CLK), GLUE1.83 (GCLK1), J2.1, RAMC1.83 (GCLK1), U17.43 (GCLK1), X1.5 (OUT)
CPU-D0: CPU1.K13 (D0), U1.A3 (D0), U4.18 (B0)
CPU-D1: CPU1.K12 (D1), U1.A4 (D1), U4.17 (B1)
CPU-D2: CPU1.L13 (D2), U1.B5 (D2), U4.16 (B2)
CPU-D3: CPU1.M13 (D3), U1.A5 (D3), U4.15 (B3)
CPU-D4: CPU1.L12 (D4), U1.A6 (D4), U4.14 (B4)
CPU-D5: CPU1.K11 (D5), U1.B6 (D5), U4.13 (B5)
CPU-D6: CPU1.M12 (D6), U1.A7 (D6), U4.12 (B6)
CPU-D7: CPU1.L11 (D7), U1.A8 (D7), U4.11 (B7)
CPU-D8: CPU1.N13 (D8), U1.A9 (D8), U5.18 (B0)
CPU-D9: CPU1.M11 (D9), U1.C8 (D9), U5.17 (B1)
CPU-D10: CPU1.L10 (D10), U1.B9 (D10), U5.16 (B2)
CPU-D11: CPU1.N12 (D11), U1.B10 (D11), U5.15 (B3)
CPU-D12: CPU1.M10 (D12), U1.D9 (D12), U5.14 (B4)
CPU-D13: CPU1.N11 (D13), U1.C9 (D13), U5.13 (B5)
CPU-D14: CPU1.M9 (D14), U1.C10 (D14), U5.12 (B6)
CPU-D15: CPU1.N10 (D15), U1.D10 (D15), U5.11 (B7)
CPU-D16: CPU1.N9 (D16), U1.F10 (D16), U6.18 (B0), U11.18 (B0)
CPU-D17: CPU1.M8 (D17), U1.F9 (D17), U6.17 (B1), U11.17 (B1)
CPU-D18: CPU1.N8 (D18), U1.G10 (D18), U6.16 (B2), U11.16 (B2)
CPU-D19: CPU1.N7 (D19), U1.H10 (D19), U6.15 (B3), U11.15 (B3)
CPU-D20: CPU1.M7 (D20), U1.G9 (D20), U6.14 (B4), U11.14 (B4)
CPU-D21: CPU1.N6 (D21), U1.J10 (D21), U6.13 (B5), U11.13 (B5)
CPU-D22: CPU1.M6 (D22), U1.K10 (D22), U6.12 (B6), U11.12 (B6)
CPU-D23: CPU1.N5 (D23), U1.J9 (D23), U6.11 (B7), U11.11 (B7)
CPU-D24: CPU1.M5 (D24), GLUE1.44 (IO65), ROM1.13 (D0), U1.K9 (D24), U7.18 (B0), U10.18 (B0), U12.18 (B0), U20.14 (D0), U24.12 (PB0), VGEN1.73 (IO115)
CPU-D25: CPU1.N4 (D25), GLUE1.45 (IO67), ROM1.14 (D1), U1.J7 (D25), U7.17 (B1), U10.17 (B1), U12.17 (B1), U20.15 (D1), U24.13 (PB1), VGEN1.74 (IO117)
CPU-D26: CPU1.N3 (D26), GLUE1.46 (IO69), ROM1.15 (D2), U1.K8 (D26), U7.16 (B2), U10.16 (B2), U12.16 (B2), U20.16 (D2), U24.14 (PB2), VGEN1.76 (IO120)
CPU-D27: CPU1.M4 (D27), GLUE1.48 (IO72), ROM1.17 (D3), U1.K7 (D27), U7.15 (B3), U10.15 (B3), U12.15 (B3), U20.17 (D3), U24.15 (PB3), VGEN1.75 (IO118)
CPU-D28: CPU1.N2 (D28), GLUE1.49 (IO73), ROM1.18 (D4), U1.J6 (D28), U7.14 (B4), U10.14 (B4), U12.14 (B4), U20.18 (D4), U24.16 (PB4), VGEN1.77 (IO123)
CPU-D29: CPU1.M3 (D29), GLUE1.50 (IO75), ROM1.19 (D5), U1.K6 (D29), U7.13 (B5), U10.13 (B5), U12.13 (B5), U20.19 (D5), U24.17 (PB5), VGEN1.80 (IO126)
CPU-D30: CPU1.L4 (D30), GLUE1.51 (IO77), ROM1.20 (D6), U1.K5 (D30), U7.12 (B6), U10.12 (B6), U12.12 (B6), U20.20 (D6), U24.18 (PB6), VGEN1.79 (IO125)
CPU-D31: CPU1.N1 (D31), GLUE1.52 (IO80), ROM1.21 (D7), U1.J5 (D31), U7.11 (B7), U10.11 (B7), U12.11 (B7), U20.21 (D7), U24.19 (PB7), VGEN1.81 (IO128)
FC0: CPU1.D2 (FC0), GLUE1.12 (IO3), RAMC1.12 (IO3)
FC1: CPU1.C1 (FC1), GLUE1.11 (IO5), RAMC1.11 (IO5)
FC2: CPU1.D1 (FC2), GLUE1.10 (IO6), RAMC1.10 (IO6)
GND: C1.2, C2.2, C3.2, C4.2, C5.2, C6.2, C7.2, C8.2, C9.2, C10.2, C11.2, C12.2, C13.2, C14.2, C15.2, C16.2, C17.2, C18.2, C19.2, C20.2, C21.2, C22.2, C23.2, C24.2, C25.2, C26.2, C27.2, C28.2, C29.2, C30.2, C31.2, C32.2, C33.2, C34.2, C35.2, C36.2, C37.2, C38.2, C39.2, C40.2, C41.2, C42.2, C43.2, C44.2, C45.2, C46.2, C47.2, C48.2, C49.2, C50.2, C51.2, C52.2, C53.2, C54.2, C55.2, C56.2, C57.2, C58.2, C59.2, C60.2, C61.2, C62.2, C63.2, C64.2, C65.2, C66.2, C67.2, C68.2, C69.2, C70.2, C71.2, C72.2, C73.2, C74.2, C75.2, C76.2, C77.2, C78.2, C79.2, C80.2, C81.2, C82.2, C83.2, C84.1, C85.1, C86.1, C87.1, C88.2, C89.2, C90.2, C91.2, C92.2, C101.2, C105.2, C108.2, C110.2, CPU1.C5 (GND), CPU1.C7 (GND), CPU1.C9 (GND), CPU1.E3 (GND), CPU1.E11 (GND), CPU1.F3 (GND), CPU1.G3 (GND), CPU1.G11 (GND), CPU1.J3 (GND), CPU1.J11 (GND), CPU1.L5 (GND), CPU1.L7 (GND), CPU1.L8 (GND), CPU1.L9 (GND), D1.1 (K), D2.1 (K), D3.1 (K), D4.1 (K), D5.1 (K), D6.1 (K), D7.1 (K), D8.1 (K), GLUE1.7 (GND), GLUE1.19 (GND), GLUE1.32 (GND), GLUE1.42 (GND), GLUE1.47 (GND), GLUE1.59 (GND), GLUE1.72 (GND), GLUE1.82 (GND), H1.1, H2.1, H3.1, H4.1, H5.1, H6.1, H7.1, H8.1, H9.1, IDE0.2, IDE0.19, IDE0.22, IDE0.24, IDE0.26, IDE0.30, IDE0.40, J1.1, J1.3, J1.5, J1.7, J1.9, J3.5, J3.6, J3.7, J3.8, J3.10, J4.1 (GND), J4.31 (GND), J4.80 (GND), J5.1 (GND), J5.31 (GND), J5.80 (GND), J6.1 (GND), J6.31 (GND), J6.80 (GND), J7.1, J8.3 (GND), J8.5 (GND), J8.7 (GND), J8.15 (GND), J8.17 (GND), J8.18 (GND), J8.19 (GND), J8.24 (GND), J9.1, J10.3, J11.5, J12.5, J13.3, P1.5, P1.6, P2.1, P2.2, PAR0.18, PAR0.19, PAR0.20, PAR0.21, PAR0.22, PAR0.23, PAR0.24, PAR0.25, Q1.1 (E), RAMC1.7 (GND), RAMC1.19 (GND), RAMC1.32 (GND), RAMC1.42 (GND), RAMC1.47 (GND), RAMC1.59 (GND), RAMC1.72 (GND), RAMC1.82 (GND), RN1.5 (R4.2), RN2.5 (R4.2), RN3.5 (R4.2), RN4.5 (R4.2), RN5.5 (R4.2), RN6.5 (R4.2), ROM1.16 (GND), SW1.2, U1.A2 (GND), U1.A10 (GND), U1.B2 (GND), U1.B3 (GND), U1.B7 (GND), U1.C1 (GND), U1.C3 (GND), U1.D2 (GND), U1.E10 (GND), U1.F2 (GND), U1.H9 (GND), U1.J8 (GND), U1.K3 (GND), U2.1 (VSS), U2.39 (VSS), U2.72 (VSS), U3.7 (GND), U4.10 (GND), U5.10 (GND), U6.10 (GND), U7.10 (GND), U8.1 (VSS), U8.39 (VSS), U8.72 (VSS), U9.3 (GND), U10.10 (GND), U11.10 (GND), U12.10 (GND), U13.10 (GND), U14.10 (GND), U15.6 (D4), U15.7 (D5), U15.8 (D6), U15.9 (D7), U15.10 (GND), U16.10 (GND), U16.11 (2A3), U17.10 (GND), U17.22 (GND), U17.30 (GND), U17.42 (GND), U18.1 (G), U18.3 (R0), U18.10 (GND), U18.15 (P6), U18.16 (R6), U18.17 (P7), U18.18 (R7), U19.3 (A1), U19.8 (GND), U20.2 (GND), U20.7 (GND), U20.43 (GND), U20.54 (GND), U21.15 (GND), U22.15 (GND), U23.5 (EI), U23.8 (GND), U24.10 (GND), VBUF1.11 (GND), VGEN1.7 (GND), VGEN1.19 (GND), VGEN1.32 (GND), VGEN1.42 (GND), VGEN1.47 (GND)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
unnamed: D1.2 (A), RN13.8 (R1.2)
unnamed: D2.2 (A), RN13.7 (R2.2)
unnamed: D3.2 (A), RN13.6 (R3.2)
unnamed: D4.2 (A), RN13.5 (R4.2)
unnamed: D5.2 (A), RN14.8 (R1.2)
unnamed: D6.2 (A), RN14.7 (R2.2)
unnamed: D7.2 (A), RN14.6 (R3.2)
unnamed: D8.2 (A), RN14.5 (R4.2)
unnamed: J2.2, U1.C2 (CLK)
unnamed: J8.1 (+3.3V), J8.2 (+3.3V), J8.12 (+3.3V), J8.13 (+3.3V)
unnamed: RN7.4 (R4.1), VBUF1.1 (OUT1)
unnamed: RN13.2 (R2.1), U3.2
unnamed: RN13.3 (R3.1), U3.4
unnamed: RN13.4 (R4.1), U3.6
unnamed: RN14.1 (R1.1), U3.8
unnamed: RN14.2 (R2.1), U3.10
unnamed: RN14.3 (R3.1), U3.12
unnamed: U18.19 (P=R), U19.1 (E)
unnamed: U24.5 (PA0/XTAL1), Y1.1
unnamed: U24.4 (PA1/XTAL2), Y1.3
unnamed: VBUF1.6 (IN2_N), VBUF1.7 (OUT2)
unnamed: VBUF1.8 (OUT3), VBUF1.9 (IN3_N)
unnamed: VBUF1.13 (IN4_N), VBUF1.14 (OUT4)
PWR_OK: GLUE1.54 (IO83), J8.8 (PWR_OK), P1.1
PWR_ON_L: GLUE1.55 (IO85), RN21.1 (R1.1)
R/~W: CPU1.L3 (R/~W), GLUE1.4 (IO16), RAMC1.5 (IO14), U1.K2 (R/~W), U10.1 (A->B), U11.1 (A->B), U12.1 (A->B), U17.6 (IO11), U24.11 (PD6), VGEN1.41 (IO49)
SIZ0: CPU1.L2 (SIZ0), GLUE1.9 (IO8), RAMC1.9 (IO8), U17.12 (IO1)
SIZ1: CPU1.K3 (SIZ1), GLUE1.8 (IO11), RAMC1.8 (IO11), U17.11 (IO3)
VCC: C1.1, C2.1, C3.1, C4.1, C5.1, C6.1, C7.1, C8.1, C9.1, C10.1, C11.1, C12.1, C13.1, C14.1, C15.1, C16.1, C17.1, C18.1, C19.1, C20.1, C21.1, C22.1, C23.1, C24.1, C25.1, C26.1, C27.1, C28.1, C29.1, C30.1, C31.1, C32.1, C33.1, C34.1, C35.1, C36.1, C37.1, C38.1, C39.1, C40.1, C41.1, C42.1, C43.1, C44.1, C45.1, C46.1, C47.1, C48.1, C49.1, C50.1, C51.1, C52.1, C53.1, C54.1, C55.1, C56.1, C57.1, C58.1, C59.1, C60.1, C61.1, C62.1, C63.1, C64.1, C65.1, C66.1, C67.1, C68.1, C69.1, C70.1, C73.1, C74.1, C76.1, C77.1, C78.1, C79.1, C80.1, C81.1, C82.1, C88.1, C89.1, C90.1, C91.1, C92.1, C101.1, C104.2, C107.2, C110.1, CPU1.C6 (Vcc), CPU1.D4 (Vcc), CPU1.D10 (Vcc), CPU1.F2 (Vcc), CPU1.F11 (Vcc), CPU1.H3 (Vcc), CPU1.H11 (Vcc), CPU1.K4 (Vcc), CPU1.K10 (Vcc), CPU1.L6 (Vcc), GLUE1.3 (VCC), GLUE1.13 (VCCIO), GLUE1.26 (VCCIO), GLUE1.38 (VCCIO), GLUE1.43 (VCC), GLUE1.53 (VCCIO), GLUE1.66 (VCCIO), GLUE1.78 (VCCIO), J4.3 (+5V), J4.29 (VCC), J4.78 (+5V), J5.3 (+5V), J5.29 (VCC), J5.78 (+5V), J6.3 (+5V), J6.29 (VCC), J6.78 (+5V), J8.4 (+5V), J8.6 (+5V), J8.21 (+5V), J8.22 (+5V), J8.23 (+5V), J10.1, J13.4, P1.2, P2.4, P2.5, P2.6, R1.1, R2.1, RAMC1.3 (VCC), RAMC1.13 (VCCIO), RAMC1.26 (VCCIO), RAMC1.38 (VCCIO), RAMC1.43 (VCC), RAMC1.53 (VCCIO), RAMC1.66 (VCCIO), RAMC1.78 (VCCIO), RN7.5 (R4.2), RN8.5 (R4.2), RN8.6 (R3.2), RN8.7 (R2.2), RN8.8 (R1.2), RN9.5 (R4.2), RN9.6 (R3.2), RN9.7 (R2.2), RN9.8 (R1.2), RN10.5 (R4.2), RN10.6 (R3.2), RN10.7 (R2.2), RN10.8 (R1.2), RN11.5 (R4.2), RN11.6 (R3.2), RN11.7 (R2.2), RN11.8 (R1.2), RN12.5 (R4.2), RN12.6 (R3.2), RN12.7 (R2.2), RN12.8 (R1.2), RN13.1 (R1.1), ROM1.32 (VCC), U1.A1 (VCC), U1.B1 (VCC), U1.B8 (VCC), U1.E2 (VCC), U1.E9 (VCC), U1.F1 (SIZE), U1.H3 (A0), U1.H8 (VCC), U1.J2 (VCC), U2.10 (VCC), U2.30 (VCC), U2.59 (VCC), U3.14 (VCC), U4.20 (VCC), U5.20 (VCC), U6.20 (VCC), U7.20 (VCC), U8.10 (VCC), U8.30 (VCC), U8.59 (VCC), U9.2 (VCC), U10.20 (VCC), U11.20 (VCC), U12.20 (VCC), U13.20 (VCC), U14.20 (VCC), U15.20 (VCC), U16.20 (VCC), U17.15 (VCC), U17.23 (VCC), U17.35 (VCC), U18.5 (R1), U18.7 (R2), U18.9 (R3), U18.12 (R4), U18.14 (R5), U18.20 (VCC), U19.16 (VCC), U20.23 (VCC), U20.27 (VCC), U20.40 (VCC), U20.64 (VCC), U21.16 (VCC), U22.16 (VCC), U23.16 (VCC), U24.20 (VCC), VBUF1.2 (IN1_N), VBUF1.3 (IN1_P), VBUF1.4 (VCC), VGEN1.3 (VCC), VGEN1.13 (VCCIO), VGEN1.26 (VCCIO), VGEN1.38 (VCCIO), VGEN1.43 (VCC), VGEN1.53 (VCCIO), VGEN1.66 (VCCIO), VGEN1.78 (VCCIO), VRAM1.28 (VCC), VRAM2.28 (VCC), X1.8 (Vcc), X2.8 (Vcc), X3.8 (Vcc), X4.8 (Vcc)
~AS: CPU1.J2 (~AS), GLUE1.6 (IO13), RAMC1.6 (IO13), U1.H1 (~AS), U17.9 (IO4)
~AVEC: CPU1.E2 (~AVEC), GLUE1.25 (IO45), RN9.4 (R4.1)
~BERR: CPU1.H1 (~BERR), GLUE1.18 (IO24), RN11.1 (R1.1), U3.5
~BGACK: CPU1.C3 (~BGACK), RN10.2 (R2.1)
~BR: CPU1.A1 (~BR), RN10.1 (R1.1)
~CBACK: CPU1.J1 (~CBACK), RN8.2 (R2.1)
~CDIS: CPU1.H12 (~CDIS), RN12.1 (R1.1)
~CIIN: CPU1.L1 (~CIIN), GLUE1.17 (IO25), RN8.1 (R1.1)
~DSACK0: CPU1.F1 (~DSACK0), GLUE1.22 (IO17), RN8.3 (R3.1), U1.J4 (~DSACK0)
~DSACK1: CPU1.G2 (~DSACK1), GLUE1.21 (IO19), RN8.4 (R4.1), U1.K4 (~DSACK1)
~DS: CPU1.K2 (~DS), GLUE1.5 (IO14), U1.G1 (~DS), U17.8 (IO5), VGEN1.6 (IO13)
~FPU-CE: GLUE1.34 (IO61), U1.J3 (~CS)
~FPU-SENSE: GLUE1.33 (IO64), RN12.4 (R4.1), U1.B4 (SENSE)
~HALT: CPU1.H2 (~HALT), RN11.3 (R3.1), U3.3
~IPL0: CPU1.H13 (~IPL0), GLUE1.29 (IO38), RN9.1 (R1.1), U23.9 (S0)
~IPL1: CPU1.G13 (~IPL1), GLUE1.28 (IO40), RN9.2 (R2.1), U23.7 (S1)
~IPL2: CPU1.G12 (~IPL2), GLUE1.27 (IO43), RN9.3 (R3.1), U23.6 (S2)
~ISA-CE: GLUE1.24 (IO46), U3.13, U17.31 (IO46)
~ISA-DACK8: GLUE1.41 (IO49), U17.33 (IO49)
~ISA-DACK16: GLUE1.40 (IO51), U17.34 (IO51)
~MEM-RD: GLUE1.16 (IO27), ROM1.24 (OE), U20.37 (~IOR)
~MEM-WR: GLUE1.15 (IO29), ROM1.31 (PGM), U20.36 (~IOW)
~MMUDIS: CPU1.F13 (~MMUDIS), RN12.2 (R2.1)
~PS2-ACK: GLUE1.58 (IO91), U24.9 (PD5)
~PS2-ATN: GLUE1.57 (IO88), U24.6 (PD2)
~RAM-CE: GLUE1.35 (IO59), RAMC1.84 (OE1), U3.11, U4.19 (CE), U5.19 (CE), U6.19 (CE), U7.19 (CE)
~RAM-DSACK: GLUE1.36 (IO57), RAMC1.33 (IO64)
~RESET: CPU1.F12 (~RESET), GLUE1.1 (GCLR), J9.2, RAMC1.1 (GCLR), RN11.2 (R2.1), SW1.1, U1.D1 (~RESET), U3.1, U9.1 (~RESET), U20.39 (~MR), U24.1 (PA2/~RESET), VGEN1.1 (GCLR)
~ROM-CE: GLUE1.31 (IO35), ROM1.22 (CE), U3.9
~SPIO-CE: GLUE1.56 (IO86), U19.15 (E)
~STERM: CPU1.G1 (~STERM), GLUE1.20 (IO21), RN10.3 (R3.1)
~VID-CE: GLUE1.30 (IO37), GLUE1.39 (IO53), VGEN1.84 (OE1)
~VID-DSACK: GLUE1.37 (IO56), VGEN1.5 (IO14)

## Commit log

2021-12-02 Add BOM
2021-12-29 New Verilog glue logic
2021-12-29 ROM Overlay Fix
2021-12-30 Initial working ROM monitor
2021-12-30 Working Enhanced BASIC
2021-12-30 Add option to skip chip erase
2021-12-30 Run BASIC from RAM
2021-12-30 Cleanup old
2021-12-30 Change UART to 38400bps
2021-12-30 Enable CPU cache
2021-12-31 TSMON 2nd UART
2021-12-31 Add 2nd UART to BASIC
2021-12-31 BASIC loader script
2021-12-31 BASIC loader bugfix
2022-01-09 Add basic SE-VGA video support
2022-01-09 BASIC test programs
2022-01-09 Update BASIC example
2022-01-09 add vertical scroll call
2022-01-10 Updated scroll routine
2022-01-16 More BASIC demos
2022-01-16 Remove ACIA TXBE hacks
2022-01-16 Shorten BASIC loader delays
2022-01-16 Refactor for 50MHz
2022-01-25 Updated BASIC examples
2022-01-25 BASIC drawChar call
2022-10-25 starting a FAT16 bootloader
2022-10-29 Mezzanine glue fpu draft
2022-12-24 Video Board Initial Schematic & Gerbers
2022-12-24 Readme formatting fix
2022-12-25 Video Board logic first draft
2022-12-26 VRAM address counter
2022-12-28 DSACK deassertion logic fix
2023-01-01 video logic debugging
2023-01-02 FPU glue logic debugging
2023-01-17 preparing for loading FPU BASIC from disk
2023-01-23 Video and FPU test programs
2023-01-28 Demo Programs
2023-01-28 srec loader for Linux
2023-02-02 New 128k ROM initial commit
2023-02-03 fix for float exponent conversion
2023-03-16 Begin Schematic Unification
2023-03-18 Schematic substantial completion
2023-03-23 PCB substantial completion
2023-03-24 Add interrupt controller to schematic
2023-03-26 Completing PCB Routing
2023-03-28 PCB Silkscreen & DRC Cleanup
2023-03-30 Initial production files
2023-03-30 initial production schematic
2023-03-31 Replace resistor nets with 0402 & update gerbers
2023-04-03 Rebase around new mATX mainboard
2023-04-24 Initial bus controller logic
2023-05-02 update busCtrl, first draft dramCtrl
2023-05-03 new cleaner bus controller logic
2023-05-04 DRAM initialization logic not needed
2023-05-05 fix address decoding bug in busCtrl logic
2023-05-19 fix DRAM controller settings register
2023-05-22 Cleanout old code, update test programs
2023-05-22 initial running port of TSMON & EhBASIC
2023-05-23 3-state busCtrl DSACKx wired-or with FPU DSACKx
2023-05-26 Fix startup overlay reset & soft power on
2023-05-26 add soft power off control to TSMON
2023-06-20 VCFSW 2023
